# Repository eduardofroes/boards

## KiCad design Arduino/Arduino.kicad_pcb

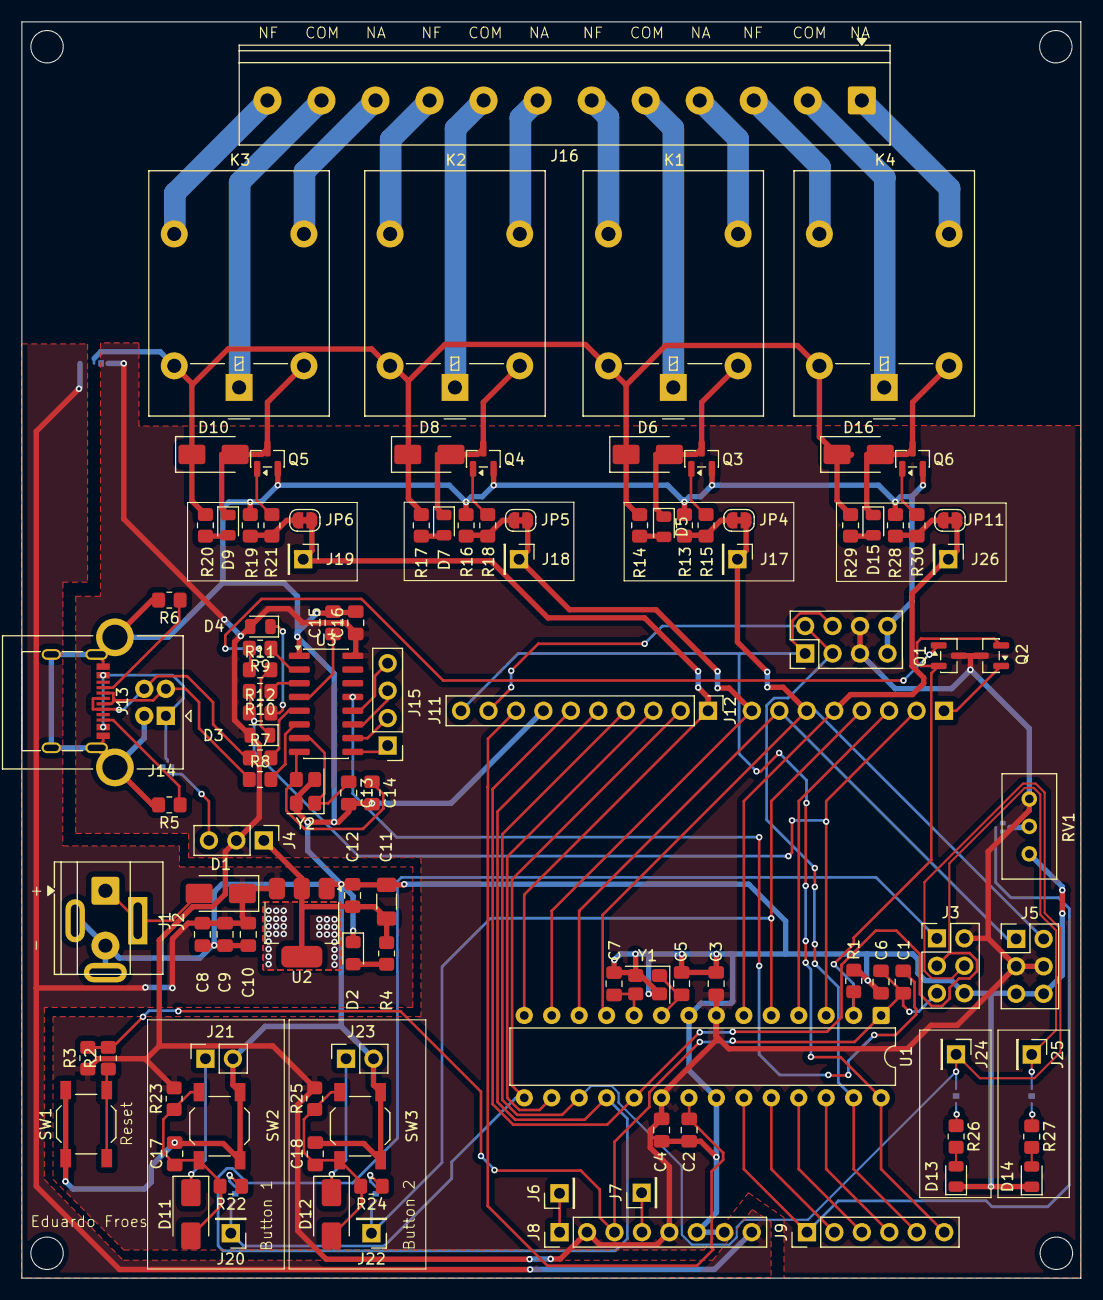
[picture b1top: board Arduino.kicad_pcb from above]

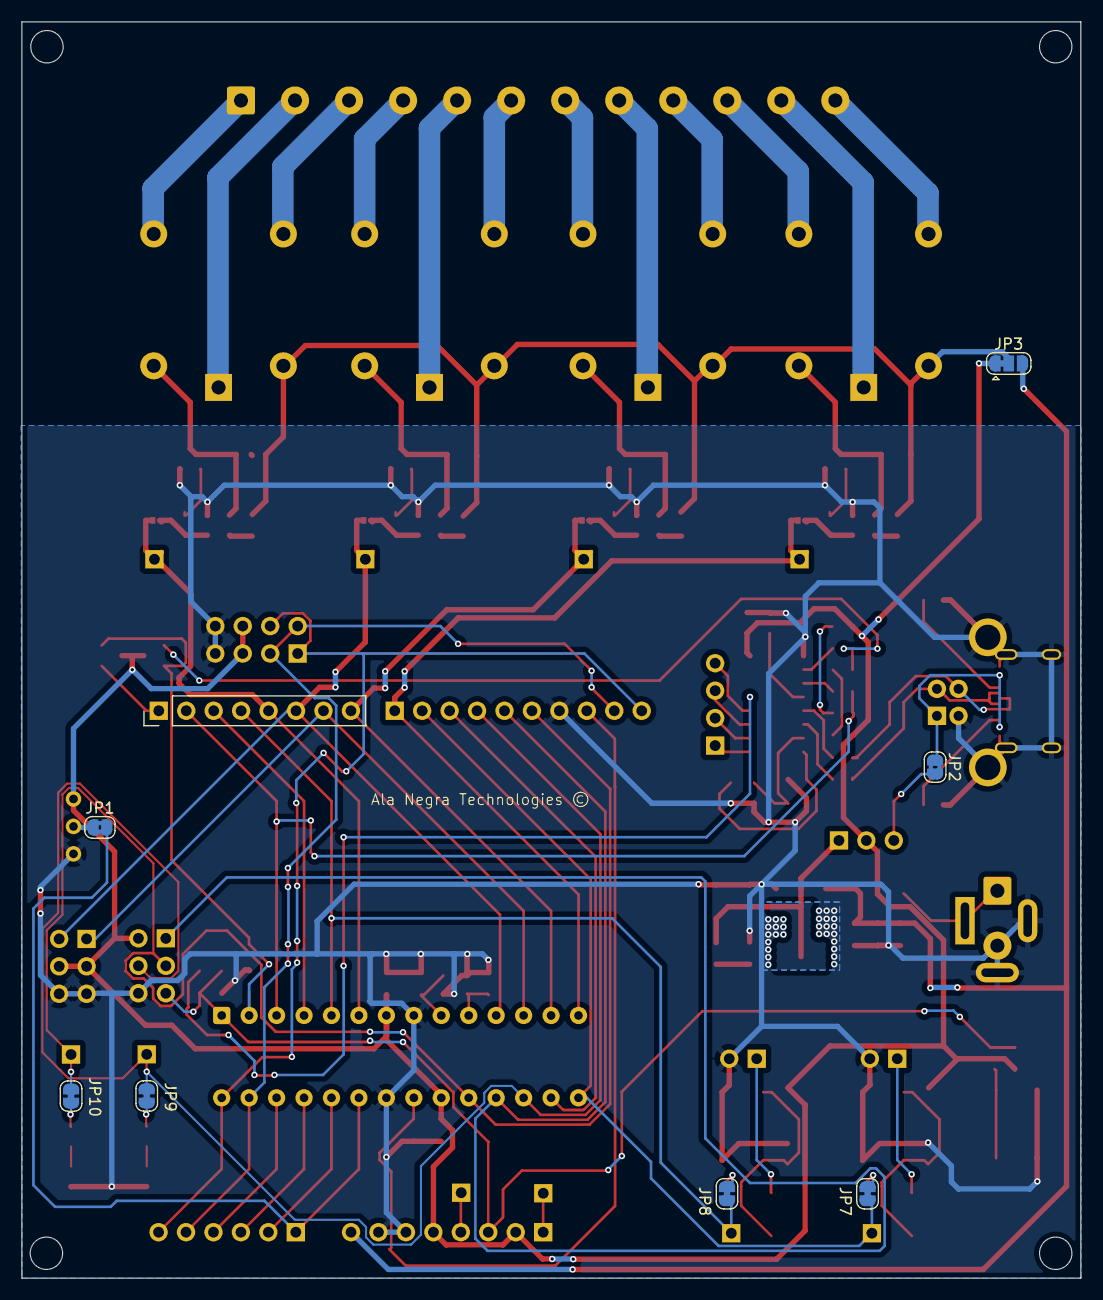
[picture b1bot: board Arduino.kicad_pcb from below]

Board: 2 copper layers, 98.0 x 116.3 mm, 120 parts (8 on the bottom side), 95 nets.

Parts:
C1, C2, C3, C4, C6, C8, C12, C17, C18: 100n; C_0805_2012Metric_Pad1.18x1.45mm_HandSolder
C5, C7: 22p; C_0805_2012Metric_Pad1.18x1.45mm_HandSolder
C9, C10: 10u 50v; C_0805_2012Metric_Pad1.18x1.45mm_HandSolder
C11: 100u 6.3v; C_1206_3216Metric_Pad1.33x1.80mm_HandSolder
C13, C14: 22pF; C_0805_2012Metric_Pad1.18x1.45mm_HandSolder
C15, C16: 100nF; C_0805_2012Metric_Pad1.18x1.45mm_HandSolder
D1, D6, D8, D10, D11, D12, D16: 1N4007; D_SMA
D2: LED; LED_0805_2012Metric_Pad1.15x1.40mm_HandSolder
D3: LED_TX; D_0805_2012Metric
D4: LED_RX; D_0805_2012Metric
D5, D7, D9, D13, D14, D15: LED; LED_0805_2012Metric
J1: Barrel_Jack_Switch; BarrelJack_Wuerth_6941xx301002
J2: Vcc; TerminalBlock_Phoenix_MKDS-1,5-2-5.08_1x02_P5.08mm_Horizont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
J3: ICSP; PinHeader_2x03_P2.54mm_Vertical
J4: Conn_01x03; PinHeader_1x03_P2.54mm_Vertical
J5: Servo; PinHeader_2x03_P2.54mm_Vertical
J6, J7, J17, J18, J19, J26: Conn_01x01; PinHeader_1x01_P2.54mm_Vertical
J8: Power; PinHeader_1x08_P2.54mm_Vertical
J9: Digital; PinHeader_1x06_P2.54mm_Vertical
J10: I2C; PinHeader_2x04_P2.54mm_Vertical
J11: Digital; PinHeader_1x10_P2.54mm_Vertical
J12: Digital; PinHeader_1x08_P2.54mm_Vertical
J13: USB_C_Receptacle_USB2.0; USB_C_Receptacle_G-Switch_GT-USB-7010ASV
J14: USB_B; USB_B_OST_USB-B1HSxx_Horizontal
J15: Conn_01x04; PinHeader_1x04_P2.54mm_Vertical
J16: Screw_Terminal_01x12; TerminalBlock_Phoenix_PT-1,5-12-5.0-H_1x12_P5.00mm_Horizont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
J20, J22, J24, J25: Pin; PinHeader_1x01_P2.54mm_Vertical
J21, J23: Bt_ext; PinSocket_1x02_P2.54mm_Vertical
JP1: A; SolderJumper-2_P1.3mm_Bridged2Bar_RoundedPad1.0x1.5mm
JP2: Vusb; SolderJumper-2_P1.3mm_Bridged2Bar_RoundedPad1.0x1.5mm
JP3: SolderJumper_3_Bridged12; SolderJumper-3_P1.3mm_Bridged12_RoundedPad1.0x1.5mm
JP4, JP5, JP6, JP7, JP8, JP9, JP10, JP11: A; SolderJumper-2_P1.3mm_Bridged_RoundedPad1.0x1.5mm
K1, K2, K3, K4: G5LE-1; Relay_SPDT_Omron-G5LE-1
Q1, Q2, Q3, Q4, Q5, Q6: SS8050; SOT-23
R1, R3, R13, R15, R16, R18, R19, R21, R28, R30: 10k; R_0805_2012Metric_Pad1.20x1.40mm_HandSolder
R2, R4, R9, R10, R11, R12, R14, R17, R20, R22, R24, R26, R27, R29: 1k; R_0805_2012Metric_Pad1.20x1.40mm_HandSolder
R5, R6: 5k1; R_0805_2012Metric_Pad1.20x1.40mm_HandSolder
R7, R8: 51; R_0805_2012Metric_Pad1.20x1.40mm_HandSolder
R23, R25: 100k; R_0805_2012Metric_Pad1.20x1.40mm_HandSolder
RV1: 100k; Potentiometer_Bourns_3296W_Vertical
SW1: Reset; SW_SPST_TL3342
SW2, SW3: Button; SW_SPST_TL3342
U1: ATmega328P-P; DIP-28_W7.62mm
U2: AMS1117-5.0; SOT-223-3_TabPin2
U3: CH340G; SOIC-16_3.9x9.9mm_P1.27mm
Y1: 16MHz; Crystal_SMD_Abracon_ABM8G-4Pin_3.2x2.5mm
Y2: 12Mhz; Crystal_SMD_Abracon_ABM8G-4Pin_3.2x2.5mm

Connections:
2: J12.3, U1.4 (PD2)
3: J12.4, J22.1, JP8.1 (A), U1.5 (PD3)
4: J12.5, J26.1, JP11.1 (A), U1.6 (PD4)
5: J5.2, J12.6, J17.1, JP4.1 (A), U1.11 (PD5)
6: J5.1, J12.7, U1.12 (PD6)
7: J12.8, J18.1, JP5.1 (A), U1.13 (PD7)
8: J11.1, J19.1, JP6.1 (A), U1.14 (PB0)
9: J11.2, J20.1, JP7.1 (A), U1.15 (PB1)
10: J11.3, U1.16 (PB2)
11: J3.4, J11.4, J24.1, JP9.1 (A), U1.17 (PB3)
12: J3.1, J11.5, U1.18 (PB4)
13: J3.3, J11.6, J25.1, JP10.1 (A), U1.19 (PB5)
+5V: C3.1, C4.1, C16.1, D3.2 (A), D4.2 (A), J3.2, J4.2, J5.3, J5.4, J8.2, J8.5, J10.5, J10.6, JP3.1 (A), Q1.3 (C), Q2.3 (C), R3.1, R23.2, R25.2, RV1.1, U1.7 (VCC), U1.20 (AVCC), U3.16 (VCC)
+12V: C8.1, C9.1, C10.1, D1.1 (K), J8.8, JP3.3 (B), U2.3 (VI)
/CH340/DTR: C1.1, U3.13 (~DTR)
/Regulador de Tensao/+5V: C11.1, C12.1, J4.1, R4.2, U2.2 (VO)
/Regulador de Tensao/Vin: D1.2 (A), J1.1, J2.1
/Reles/Rele 1/+12V: D6.1 (K), D8.1 (K), D10.1 (K), D16.1 (K), JP3.2 (C), K1.5, K2.5, K3.5, K4.5, R14.1, R17.1, R20.1, R29.1
/Reles/Rele 1/COM: J16.2, K4.1
/Reles/Rele 1/NA: J16.1, K4.3
/Reles/Rele 1/NF: J16.3, K4.4
/Reles/Rele 2/COM: J16.5, K1.1
/Reles/Rele 2/NA: J16.4, K1.3
/Reles/Rele 2/NF: J16.6, K1.4
/Reles/Rele 3/COM: J16.8, K2.1
/Reles/Rele 3/NA: J16.7, K2.3
/Reles/Rele 3/NF: J16.9, K2.4
/Reles/Rele 4/COM: J16.11, K3.1
/Reles/Rele 4/NA: J16.10, K3.3
/Reles/Rele 4/NF: J16.12, K3.4
A0: J9.1, JP1.2 (B), U1.23 (PC0)
A1: J9.2, U1.24 (PC1)
A2: J9.3, U1.25 (PC2)
A3: J9.4, U1.26 (PC3)
A4: J9.5, J10.2, J10.3, J11.9, U1.27 (PC4)
A5: J9.6, J10.1, J10.4, J11.10, U1.28 (PC5)
Aref: C2.1, J11.8, U1.21 (AREF)
GND: C2.2, C3.2, C4.2, C5.2, C6.2, C7.2, C8.2, C9.2, C10.2, C11.2, C12.2, C13.2, C14.2, C15.2, C16.2, C17.2, C18.2, D2.1 (K), D13.1 (K), D14.1 (K), J1.2, J1.3, J2.2, J3.6, J5.5, J5.6, J8.6, J8.7, J10.7, J10.8, J11.7, J13.A1 (GND), J13.A12 (GND), J13.B1 (GND), J13.B12 (GND), J13.S1 (SHIELD), J14.4 (GND), J14.5 (Shield), J21.2, J23.2, Q3.2 (E), Q4.2 (E), Q5.2 (E), Q6.2 (E), R1.1, R5.2, R6.2, R13.2, R16.2, R19.2, R28.2, RV1.3, SW1.1 (A), SW2.1 (A), SW3.1 (A), U1.8 (GND), U1.22 (GND), U2.1 (GND), U3.1 (GND), Y1.2, Y1.4, Y2.2, Y2.4
unnamed: D2.2 (A), R4.1
unnamed: D3.1 (K), R11.2
unnamed: D4.1 (K), R12.2
unnamed: D5.2 (A), R14.2
unnamed: D5.1 (K), D6.2 (A), K1.2, Q3.3 (C)
unnamed: D7.2 (A), R17.2
unnamed: D7.1 (K), D8.2 (A), K2.2, Q4.3 (C)
unnamed: D9.2 (A), R20.2
unnamed: D9.1 (K), D10.2 (A), K3.2, Q5.3 (C)
unnamed: C17.1, D11.2 (A), R22.2, R23.1, SW2.2 (A)
unnamed: D11.1 (K), J21.1
unnamed: C18.1, D12.2 (A), R24.2, R25.1, SW3.2 (A)
unnamed: D12.1 (K), J23.1
unnamed: D13.2 (A), R26.2
unnamed: D14.2 (A), R27.2
unnamed: D15.2 (A), R29.2
unnamed: D15.1 (K), D16.2 (A), K4.2, Q6.3 (C)
unnamed: J6.1, J8.1
unnamed: J7.1, J8.4
unnamed: J13.A5 (CC1), R6.1
unnamed: J13.B5 (CC2), R5.1
unnamed: J13.A6 (D+), J13.B6 (D+), J14.3 (D+), R7.1
unnamed: J13.A7 (D-), J13.B7 (D-), J14.2 (D-), R8.1
unnamed: J13.A4 (VBUS), J13.A9 (VBUS), J13.B4 (VBUS), J13.B9 (VBUS), J14.1 (VBUS), JP2.1 (A)
unnamed: J15.1, U3.9 (~CTS)
unnamed: J15.2, U3.10 (~DSR)
unnamed: J15.3, U3.11 (~RI)
unnamed: J15.4, U3.12 (~DCD)
unnamed: JP1.1 (A), RV1.2
unnamed: JP4.2 (B), R13.1, R15.1
unnamed: JP5.2 (B), R16.1, R18.1
unnamed: JP6.2 (B), R19.1, R21.1
unnamed: JP7.2 (B), R22.1
unnamed: JP8.2 (B), R24.1
unnamed: JP9.2 (B), R26.1
unnamed: JP10.2 (B), R27.1
unnamed: JP11.2 (B), R28.1, R30.1
unnamed: Q3.1 (B), R15.2
unnamed: Q4.1 (B), R18.2
unnamed: Q5.1 (B), R21.2
unnamed: Q6.1 (B), R30.2
unnamed: R2.1, SW1.2 (A)
unnamed: R10.1, U3.3 (RXD)
unnamed: R9.1, U3.2 (TXD)
unnamed: R7.2, U3.5 (UD+)
unnamed: R8.2, U3.6 (UD-)
unnamed: C15.1, U3.4 (V3)
unnamed: C13.1, U3.7 (XI), Y2.1
unnamed: C14.1, U3.8 (XO), Y2.3
RX: Q1.2 (E), Q2.2 (E), R1.2, U1.2 (PD0)
RX1: Q1.1 (B), R9.2, R11.1
RX2: J12.1, Q2.1 (B)
Reset: C1.2, C6.1, J3.5, J8.3, R2.2, R3.2, U1.1 (~RESET/PC6)
TX: J12.2, R10.2, R12.1, U1.3 (PD1)
Vusb: J4.3, JP2.2 (B)
xtal1: C5.1, U1.9 (XTAL1/PB6), Y1.1
xtal2: C7.1, U1.10 (XTAL2/PB7), Y1.3

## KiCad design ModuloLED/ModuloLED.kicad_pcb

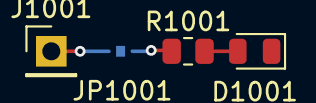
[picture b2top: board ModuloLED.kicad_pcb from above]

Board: 2 copper layers, 4 parts (1 on the bottom side), 3 nets.

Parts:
D1001: LED; LED_0805_2012Metric
J1001: Pin; PinHeader_1x01_P2.54mm_Vertical
JP1001: A; SolderJumper-2_P1.3mm_Bridged_RoundedPad1.0x1.5mm
R1001: 1k; R_0805_2012Metric

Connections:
/IN: J1001.1, JP1001.1 (A)
unnamed: D1001.2 (A), R1001.2
unnamed: JP1001.2 (B), R1001.1

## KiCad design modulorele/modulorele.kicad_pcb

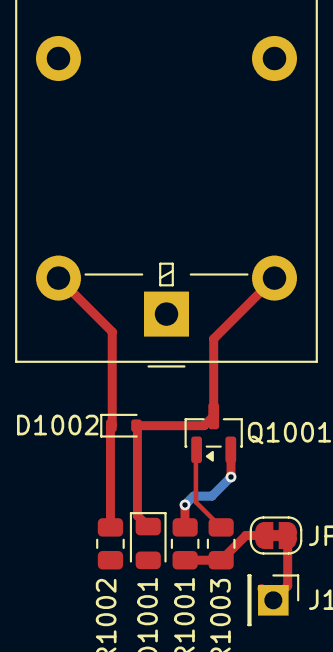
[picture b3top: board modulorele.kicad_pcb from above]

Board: 2 copper layers, 9 parts (0 on the bottom side), 7 nets.

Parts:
D1001: LED; LED_0805_2012Metric
D1002: 1N4148WT; D_SOD-523
J1001: Conn_01x01; PinHeader_1x01_P2.54mm_Vertical
JP1001: SolderJumper-2_P1.3mm_Bridged_RoundedPad1.0x1.5mm
K1001: G5LE-1; Relay_SPDT_Omron-G5LE-1
Q1001: SS8050; SOT-23
R1001, R1003: 10k; R_0805_2012Metric
R1002: 1k; R_0805_2012Metric

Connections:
/12V: D1002.1 (K), K1001.5, R1002.1
/GND: Q1001.2 (E), R1001.2
/INPUT: J1001.1, JP1001.1 (A)
unnamed: D1001.2 (A), R1002.2
unnamed: D1001.1 (K), D1002.2 (A), K1001.2, Q1001.3 (C)
unnamed: JP1001.2 (B), R1001.1, R1003.1
unnamed: Q1001.1 (B), R1003.2

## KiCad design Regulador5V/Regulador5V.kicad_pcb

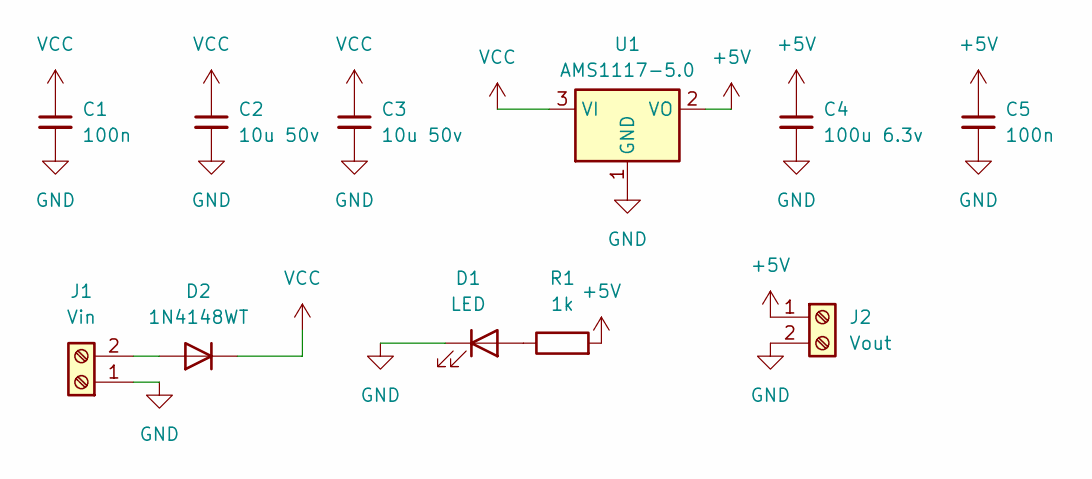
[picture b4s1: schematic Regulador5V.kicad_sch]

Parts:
C1, C5: 100n; C_0805_2012Metric_Pad1.18x1.45mm_HandSolder
C2, C3: 10u 50v; C_0805_2012Metric_Pad1.18x1.45mm_HandSolder
C4: 100u 6.3v; C_1206_3216Metric_Pad1.33x1.80mm_HandSolder
D1: LED; LED_0805_2012Metric_Pad1.15x1.40mm_HandSolder
D2: 1N4148WT; D_SOD-523
J1: Vin; TerminalBlock_Phoenix_MKDS-1,5-2_1x02_P5.00mm_Horizontal
J2: Vout; TerminalBlock_Phoenix_MKDS-1,5-2_1x02_P5.00mm_Horizontal
R1: 1k; R_0805_2012Metric_Pad1.20x1.40mm_HandSolder
U1: AMS1117-5.0; SOT-223-3_TabPin2

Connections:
+5V: C4.1, C5.1, J2.1, R1.2, U1.2 (VO)
GND: C1.2, C2.2, C3.2, C4.2, C5.2, D1.1 (K), J1.1, J2.2, U1.1 (GND)
unnamed: D1.2 (A), R1.1
unnamed: D2.2 (A), J1.2
VCC: C1.1, C2.1, C3.1, D2.1 (K), U1.3 (VI)

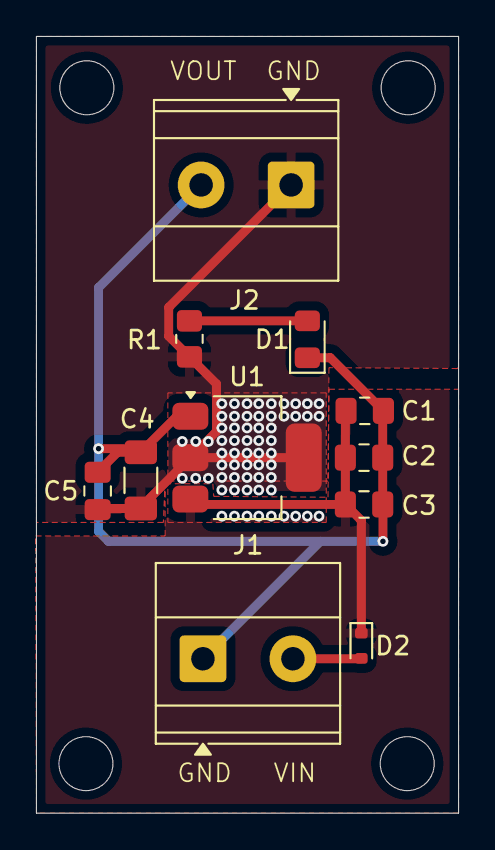
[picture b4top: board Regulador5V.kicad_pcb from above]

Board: 2 copper layers, 23.4 x 43.2 mm, 11 parts (0 on the bottom side), 5 nets.

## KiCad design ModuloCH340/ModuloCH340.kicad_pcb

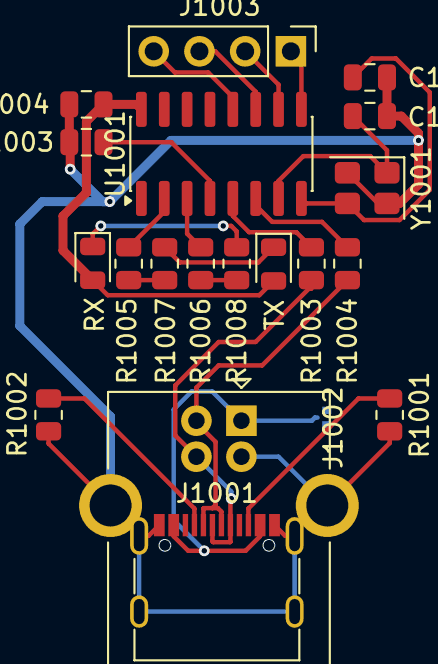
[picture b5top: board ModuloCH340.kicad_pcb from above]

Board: 2 copper layers, 20 parts (1 on the bottom side), 22 nets.

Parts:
C1001, C1002: 22pF; C_0805_2012Metric
C1003, C1004: 100nF; C_0805_2012Metric
J1001: USB_C_Receptacle_USB2.0; USB_C_Receptacle_G-Switch_GT-USB-7010ASV
J1002: USB_B; USB_B_OST_USB-B1HSxx_Horizontal
J1003: Conn_01x04; PinHeader_1x04_P2.54mm_Vertical
JP1001: Vusb; SolderJumper-2_P1.3mm_Bridged2Bar_RoundedPad1.0x1.5mm
R1001, R1002: 5k1; R_0805_2012Metric
R1003, R1004: 51; R_0805_2012Metric
R1005, R1006, R1007, R1008: 1k; R_0805_2012Metric
RX: LED_RX; D_0805_2012Metric
TX: LED_TX; D_0805_2012Metric
U1001: CH340G; SOIC-16_3.9x9.9mm_P1.27mm
Y1001: 12Mhz; Crystal_SMD_Abracon_ABM8G-4Pin_3.2x2.5mm

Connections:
/GND: C1001.2, C1002.2, C1003.2, C1004.2, J1001.A1 (GND), J1001.A12 (GND), J1001.B1 (GND), J1001.B12 (GND), J1001.S1 (SHIELD), J1002.4 (GND), J1002.5 (Shield), R1001.2, R1002.2, U1001.1 (GND), Y1001.2, Y1001.4
/RX: R1006.2, R1008.1
/TX: R1005.2, R1007.1
/Vcc: C1004.1, RX.2 (A), TX.2 (A), U1001.16 (VCC)
unnamed: R1007.2, TX.1 (K)
unnamed: R1008.2, RX.1 (K)
unnamed: J1001.A5 (CC1), R1002.1
unnamed: J1001.B5 (CC2), R1001.1
unnamed: J1001.A6 (D+), J1001.B6 (D+), J1002.3 (D+), R1003.1
unnamed: J1001.A7 (D-), J1001.B7 (D-), J1002.2 (D-), R1004.1
unnamed: J1001.A4 (VBUS), J1001.A9 (VBUS), J1001.B4 (VBUS), J1001.B9 (VBUS), J1002.1 (VBUS), JP1001.1 (A)
unnamed: J1003.1, U1001.9 (~CTS)
unnamed: J1003.2, U1001.10 (~DSR)
unnamed: J1003.3, U1001.11 (~RI)
unnamed: J1003.4, U1001.12 (~DCD)
unnamed: R1006.1, U1001.3 (RXD)
unnamed: R1005.1, U1001.2 (TXD)
unnamed: R1003.2, U1001.5 (UD+)
unnamed: R1004.2, U1001.6 (UD-)
unnamed: C1003.1, U1001.4 (V3)
unnamed: C1001.1, U1001.7 (XI), Y1001.1
unnamed: C1002.1, U1001.8 (XO), Y1001.3

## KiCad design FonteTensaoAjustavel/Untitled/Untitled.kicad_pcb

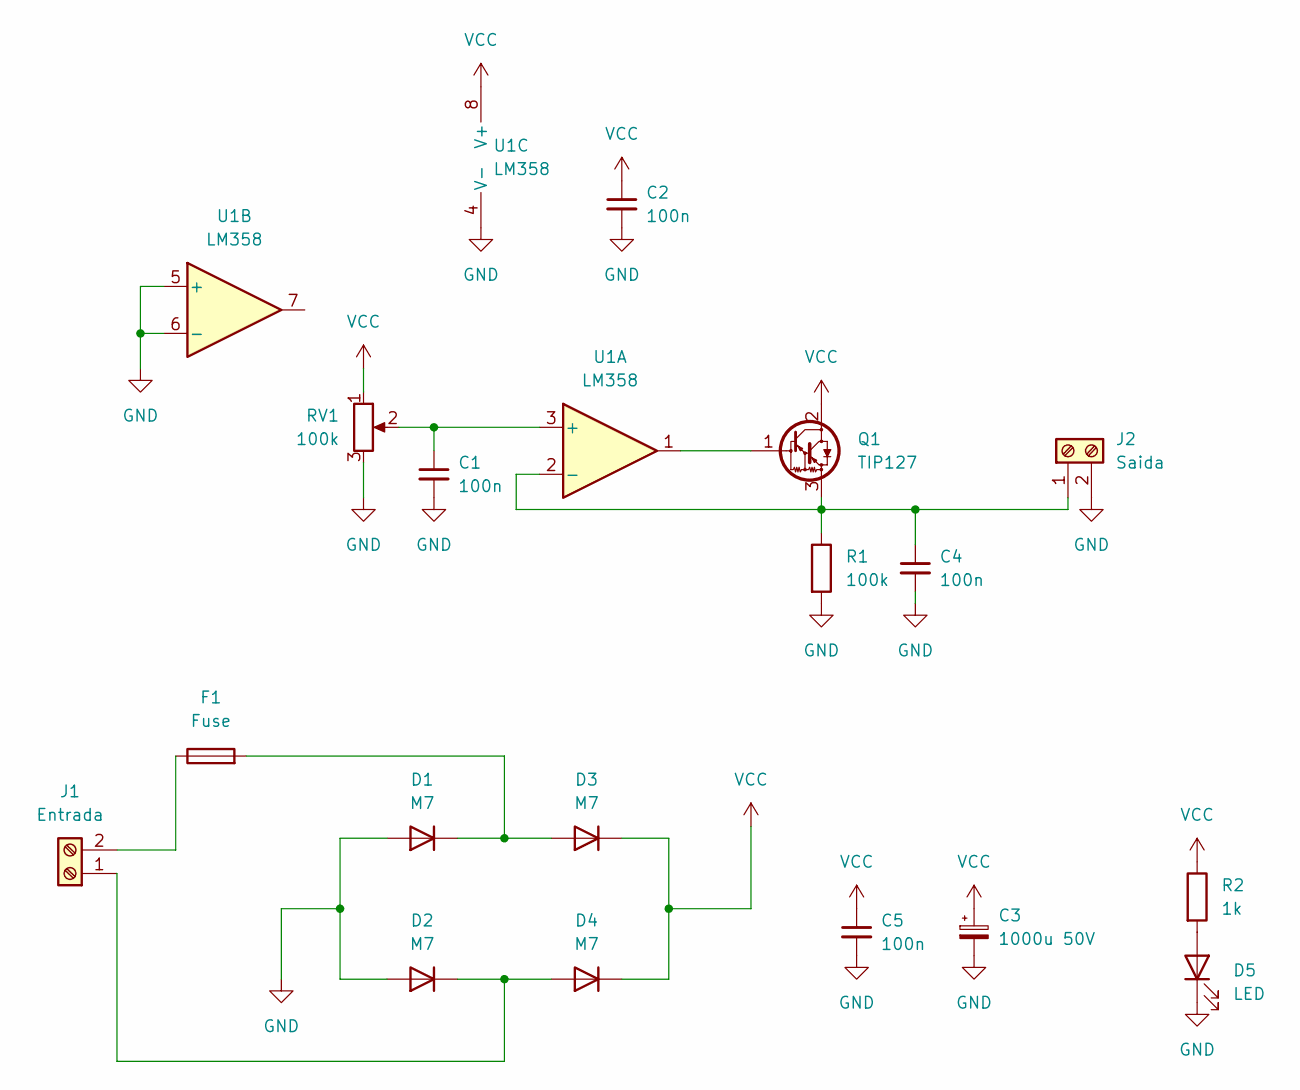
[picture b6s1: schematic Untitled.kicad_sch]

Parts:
C1, C2, C4, C5: 100n; C_0805_2012Metric_Pad1.18x1.45mm_HandSolder
C3: 1000u 50V; CP_Radial_D13.0mm_P5.00mm
D1, D2, D3, D4: M7; D_SOD-523
D5: LED; LED_0805_2012Metric_Pad1.15x1.40mm_HandSolder
F1: Fuse; Fuseholder_Cylinder-5x20mm_Schurter_0031_8201_Horizontal_Op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
J1: Entrada; TerminalBlock_Phoenix_MKDS-1,5-2_1x02_P5.00mm_Horizontal
J2: Saida; TerminalBlock_Phoenix_MKDS-1,5-2_1x02_P5.00mm_Horizontal
Q1: TIP127; TO-220-3_Horizontal_TabDown
R1: 100k; R_0805_2012Metric_Pad1.20x1.40mm_HandSolder
R2: 1k; R_0805_2012Metric_Pad1.20x1.40mm_HandSolder
RV1: 100k; PinHeader_1x03_P2.54mm_Vertical
U1: LM358; SOIC-8_3.9x4.9mm_P1.27mm

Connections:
GND: C1.2, C2.2, C3.2, C4.2, C5.2, D1.2 (A), D2.2 (A), D5.1 (K), J2.2, R1.2, RV1.3, U1.4 (V-), U1.5 (+), U1.6 (-)
unnamed: D1.1 (K), D3.2 (A), F1.2
unnamed: D2.1 (K), D4.2 (A), J1.1
unnamed: D5.2 (A), R2.2
unnamed: F1.1, J1.2
unnamed: C4.1, J2.1, Q1.3 (E), R1.1, U1.2 (-)
unnamed: Q1.1 (B), U1.1
unnamed: C1.1, RV1.2, U1.3 (+)
VCC: C2.1, C3.1, C5.1, D3.1 (K), D4.1 (K), Q1.2 (C), R2.1, RV1.1, U1.8 (V+)

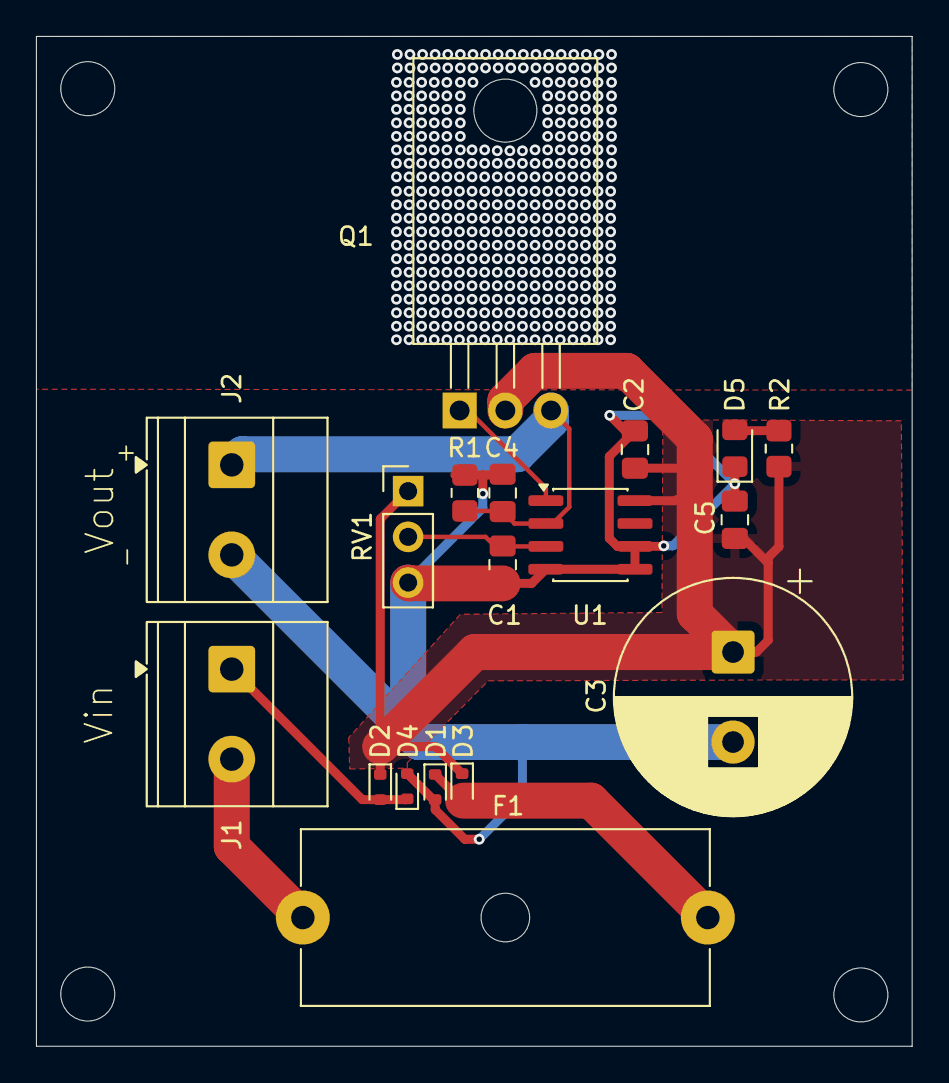
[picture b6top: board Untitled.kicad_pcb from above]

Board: 2 copper layers, 48.6 x 56.1 mm, 18 parts (0 on the bottom side), 9 nets.

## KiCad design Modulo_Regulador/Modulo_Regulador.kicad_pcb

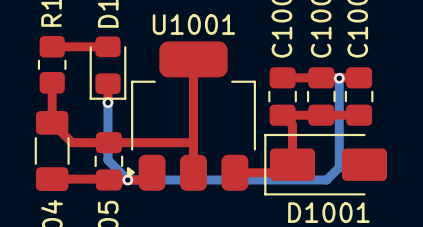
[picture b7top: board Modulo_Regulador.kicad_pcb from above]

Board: 2 copper layers, 9 parts (0 on the bottom side), 4 nets.

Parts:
C1001, C1005: 100n; C_0805_2012Metric_Pad1.18x1.45mm_HandSolder
C1002, C1003: 10u 50v; C_0805_2012Metric_Pad1.18x1.45mm_HandSolder
C1004: 100u 6.3v; C_1206_3216Metric_Pad1.33x1.80mm_HandSolder
D1001: 1N4007; D_SMA
D1002: LED; LED_0805_2012Metric_Pad1.15x1.40mm_HandSolder
R1001: 1k; R_0805_2012Metric_Pad1.20x1.40mm_HandSolder
U1001: AMS1117-5.0; SOT-223-3_TabPin2

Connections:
/5V: C1004.1, C1005.1, R1001.2, U1001.2 (VO)
/12V: C1001.1, C1002.1, C1003.1, D1001.1 (K), U1001.3 (VI)
/GND: C1001.2, C1002.2, C1003.2, C1004.2, C1005.2, D1002.1 (K), U1001.1 (GND)
unnamed: D1002.2 (A), R1001.1

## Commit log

2026-02-12 Init commit.
2026-02-20 Some changes in arduino board.
2026-02-24 New button module.
2026-02-25 Completed circuit.
2026-02-25 Added all components to arduino pcb.
2026-02-27 First version from PCB schematic.
2026-02-27 Final version of arduino board.
2026-02-28 Final adjustments in arduino board
